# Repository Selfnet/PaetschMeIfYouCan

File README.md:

# P-tschMeIfYouCan
Ein Geschicklichkeitsspiel mit Spaß am Gerät

## Important: Name Entry Keyboard Behavior

This is a required interaction contract. Preserve it when changing the dashboard:

- **Enter in the first displayed input:** move to the second input if its name is empty or whitespace-only; otherwise submit both names and proceed to the leaderboard.
- **Enter in the second displayed input:** submit both names and proceed to the leaderboard, even when either name is blank. Empty or whitespace-only names skip that player's leaderboard entry.
- **Tab / Shift+Tab:** cycle between the name inputs, including wrapping; never submit names or advance to the leaderboard, even when both names are filled.

The inputs are displayed in result order (winner first), not fixed player-number order. These rules apply regardless of which player wins or whether the race is tied. Automatic name-entry timeout is separate from keyboard submission.

[Keyboard regression tests](Test_Server/tests/test_name_entry_keyboard.py) execute the dashboard's actual JavaScript handler. Run them when changing name entry or keyboard handling; they do not test live serial hardware.

## Leaderboard Policy

Each leaderboard shows one row per case-insensitive name, separately for each game mode and leaderboard identity (numbered or named event). Ranks compare each player's **best time**; equal times share a rank. The name uses the latest spelling, and **Set at** is the best attempt's timestamp (the latest matching attempt for equal best times). The **Attempts** column counts all saved scores for that name in the same mode and board, including historical scores. Blank names are still skipped, and retrying a score save does not add an attempt.

First place, including tied first places, is displayed as **Top of Rack**; other ranks remain numeric.

After a race, that player's row is highlighted even when the new time is worse. A worse time appears as **This race** beneath the best time without changing the rank. A first score or strictly improved best earns a compact orange **New PB!** badge; matching an existing best does not. Idle browsing does not show current-race details or badges.

All attempt history remains in SQLite; grouping does not delete or rewrite scores and requires no database migration. A paginated browse freezes the best times, latest attempts, and counts at its opening snapshot. [Leaderboard regression tests](Test_Server/tests/test_leaderboard.py) cover case-insensitive grouping, best-time ranking, attempt counts, and snapshot pagination; [transport tests](Test_Server/tests/test_app.py) cover current-race highlighting and personal-best detection. Neither covers physical hardware or browser layout.

### Explicit Requirement: Post-Race Score Position

When players finish and the post-race leaderboard opens after name entry,
automatically scroll to the faster player from this race and place that
player's score row at the top of the visible list. Choose by this race's time,
not historical personal-best rank. Players must immediately see their placing
without manually searching or scrolling, including beyond the first page.
Preserve the actual leaderboard order and ranks; this requirement changes the
initial scroll position, not the standings.

This is an explicit user requirement. The jump happens once per result view;
manual navigation takes precedence. Ties choose Player 1. If the faster player
skips their name, use the other saved participant; if both skip, stay at the top.
Case-insensitive matching uses the participant's grouped personal-best row.
[Positioning tests](Test_Server/tests/test_result_position.py) cover winner
selection, pagination, ties, skipped names and manual-scroll preservation;
they do not replace native-browser geometry checks.

### Explicit Decision: Current Race Time

The post-race leaderboard must still show the current race time. The main time
and rank remain the player's personal best. If this race was slower, show its
time separately as **This race** beneath the best; if it matched or improved
the best, the main time already shows this race's time. Do not replace or hide
the current result just because an older personal best is faster. Idle browsing
does not show this post-race detail.

### Failed Score Saves

If saving fails while results are open, **Retry saving** resends the captured race,
names, times, mode and captured leaderboard. Automatic return pauses until saving succeeds, then
the leaderboard refreshes and its normal 60-second countdown restarts. Repeated
retries do not add attempts, including when a previous write committed before
reporting an error. Name-entry timeouts and skipped blank names are unchanged.

Back to game, L, Escape and Space require confirmation before abandoning failed
results. Leaving, reset and expiry are blocked during every pending write, including
the initial save. Confirmation gives
up recovery; it does not remove any scores already written. Browser refresh or
reconnection restores recovery from server state, but **restarting the backend
loses unsaved results held in memory**. This is not a durable retry queue.

Browsing another board never dismisses these results. The captured score destination,
save error and Retry saving control remain visible there. A completed save refreshes
the current page snapshot without redirecting an explicitly browsed board.

[Recovery tests](Test_Server/tests/test_score_recovery.py) cover identity,
concurrent requests, idempotence and timeout boundaries;
[recovery UI tests](Test_Server/tests/test_score_recovery_ui.py) execute the actual
dashboard handlers for confirmation, refresh and page invalidation. Neither
replaces browser layout checks or tests live hardware.

## Leaderboard Slots

Use **1-9**, including the numeric keypad, or the slot selector while the game is ready. Outside an active event this selects the next race's scoring slot and switches an open view. During an event, or while stopped or viewing post-race results, it only browses the numbered board. Event-locked digits from the game view open that board for visible feedback. Racing, name entry, maintenance and open dialogs guard the underlying shortcuts. Digits typed into inputs remain input.

Each slot has independent scores and ranks for every game mode. Switching never deletes scores. The manual selection and its selection time are saved in SQLite, independently of browser storage. An event that ends after that selection makes the effective default slot 1, including when the backend was offline for the whole event. Selecting a slot again, even the previously stored slot, records a fresh choice. The destination is captured at race start, so delayed writes cannot move a race to another board.

The database remains at `LEADERBOARD_DB` or `~/.local/share/patchmeifyoucan/leaderboard.sqlite3`. The event migration creates permanent numbered board records and replaces score slot references with stable `leaderboard_id` references. Existing scores keep their IDs, names, durations, timestamps, modes, race/player identities and numbered associations. The manual slot and maintenance setting are retained; migration creates no events. Take fresh verified database and source backups before deployment. Source-only rollback to slot-only code is unsupported, and a database rollback discards scores recorded since its backup.

[Slot persistence and transport tests](Test_Server/tests/test_leaderboard_slots.py) cover migration, isolation, restart restoration, failed settings writes, race identity, and stale page rejection; they do not exercise physical hardware. [Slot keyboard tests](Test_Server/tests/test_leaderboard_slot_keyboard.py) execute the actual dashboard shortcut and selection helpers, including modifier, focus, and phase guards; they do not replace browser layout checks.

## Event Leaderboards

Named events are independent boards, not names attached to slots. Each creation
starts empty, including when its name matches another event. One schedule applies
to all modes, with separate rankings, personal bests, attempt counts and pace
references for each board and mode. Names are trimmed printable text of 1-60
Unicode code points and are displayed as text.

The server assigns both players to the event active at race start, on the half-open
window `start <= now < end`. An active event locks scoring even when a display is
browsing another board. Name entry, delayed saves and retries keep that captured
identity after expiry or End now. Expiry changes future defaults to slot 1 (or an
adjacent active event), never an existing race or explicitly opened view. Race
duration still uses the monotonic clock; event eligibility uses the server's UTC
wall clock. Keep the server clock correct.

The main header shows the currently active event beside the game title in grey,
independent of the viewed leaderboard or captured race. It hides the event name
when no event is active or the display is disconnected.

**L** toggles the leaderboard as before. Opening from the game defaults to the
active event, otherwise the effective numbered selection. Automatic post-race
results always open the captured board. **0**, including the keypad, returns to
the active event and does nothing without one. The Current event button is its
pointer equivalent. Named titles read `Leaderboard - <event name>`; numbered titles
read `Leaderboard`, with the slot shown in the selector. The compact status shows
the next race's destination, or the captured destination while a race is unresolved.

**E** or Past events opens the archive picker only from an open leaderboard.
Events appear newest-ended first, including empty boards, with their Berlin time
ranges. Arrows move focus, Enter selects, Tab stays in the dialog, and Escape/E
closes it and restores focus to Past events. Reopening fetches a fresh list; late
responses cannot reopen a closed picker. The picker blocks underlying shortcuts,
but normal inactivity expiry still closes it. Archive browsing is local and never
redirects scoring or another display. Global manual numbered changes update
ordinary numbered views without evicting archives. Board changes start a fresh
pagination snapshot; renames update titles without losing rows or focus. Current-race
highlighting and winner positioning apply only on the captured result board.

At **/control**, Event leaderboards offers creation, editing, End now and cancellation.
All entered dates/times mean **Europe/Berlin**, even on a browser in another zone.
Start now and event statuses use server time, independent of the browser clock.
The form shows the range before submission; the server
rejects invalid names, overlapping windows, ambiguous/nonexistent DST times and
stale revisions. Rejected or timed-out changes retain inputs and show an error.
Reload events explicitly reloads the selected edit after checking a stale or
unconfirmed change. No change is accepted before storage commits it.

Upcoming events can change their full window or be cancelled after confirmation.
Active events can change their future end or use confirmed End now; their start is
fixed. End now at exactly the start is rejected without changes to preserve a
positive window; retry once server time has advanced. Past events can only be
renamed. There is no past-event or score deletion,
recurrence, historical score move, or added authentication. The control page remains
on the existing trusted-network boundary.

Unknown routing metadata blocks new races visibly instead of choosing a fallback
board. **Retry storage** reloads/reinitializes it without resetting an in-memory
race, recovery or maintenance. After a successful load, the last committed schedule
continues to route while storage is failing. Failed metadata writes cannot change
that schedule. Out-of-band database edits are not supported.

[Policy tests](Test_Server/tests/test_event_policy.py), [storage tests](Test_Server/tests/test_event_storage.py)
and [runtime tests](Test_Server/tests/test_event_runtime.py) cover schedule boundaries,
Berlin/DST validation, migration, immutable capture, revision checks and recovery.
[Player UI tests](Test_Server/tests/test_event_ui.py) and [operator UI tests](Test_Server/tests/test_event_controls.py)
execute the actual JavaScript with controlled DOM/Socket.IO boundaries; they do not
replace native-browser focus/layout checks or physical hardware tests.

## Live Race Statistics

During racing, patches/min uses the median personal-best time from the selected
mode and captured leaderboard as a starting weight of three patches. Each name
counts once, matching the leaderboard; zero-time bests are excluded. The median
is captured once per race and retained on reconnect. Empty or unavailable
leaderboards fall back to the player's own pace. Browsing another board never
changes a running race's reference.

After progress changes, the estimate holds for one estimated patching interval,
then declines if no further progress arrives. The historical weight becomes less
significant as patches accumulate. The rate stays zero before a timed patch; stopped
and completed players show their actual race average. The combined rate uses the
longer player's elapsed time, as before. These display estimates never affect
race times, winners or saved scores.

Each player's lead indicator sits between progress and the clock. Comparable
progress shows the patch gap, with the leading player's indicator highlighted;
ties are neutral and different mode stages are not compared.
[Rate and lead tests](Test_Server/tests/test_dashboard_rates.py) exercise the real
dashboard calculation and rendering; they do not verify kiosk layout or hardware.

## Maintenance Mode

Use the **Maintenance mode** checkbox at `/control` to enable or disable it.
The control page reports **Off**, **Queued** or **Active**. Enabling while ready
activates immediately, including idle leaderboard browsing. During a race,
stopped game, name entry or post-race results, it waits for the normal return to
ready. It never stops a race or dismisses results itself. Uncheck it to cancel
a queued request. A stopped game still needs its normal reset.

While active, every connected dashboard is darkened behind large lowercase
**maintenance mode** text in Selfnet orange and Comic Neue. Dashboard controls
and shortcuts cannot start a game or dismiss the overlay. Disable maintenance
from `/control` to return to ready. Serial observations continue for diagnostics.
Maintenance is an operator convenience on the existing trusted game network,
not authentication or an authorization boundary.

The request is saved in SQLite before it is accepted and is restored across
browser refreshes and backend restarts. A queued request becomes active on
backend restart because races are memory-only. **Do not restart to force queued
maintenance:** it would lose the current race or unsaved results. Failed score
saves still require retry or explicit abandonment; queued maintenance waits for
in-flight saves as well. Failed maintenance-setting writes leave the live setting
unchanged and show an error on `/control`.

Explicit operator policy: if the setting cannot be read at backend startup,
log the error and leave maintenance off. This does not override the separate event
routing safety rule: unknown routing metadata blocks new races until Retry storage
succeeds. A readable saved setting is required for restart
persistence. Migration only adds a default-off settings column; it does not
change scores or the selected slot. Pre-maintenance source ignores this setting,
so a source rollback will no longer block games. Take a fresh database backup
before deployment; maintenance does not itself authorize deployment or restart.

Comic Neue is the approved open-source substitute for Comic Sans. Its bold font
is bundled and served locally, with no OS font installation or external request.
[Dashboard assets](Test_Server/static/dashboard/README.md) records its source and
OFL license; verify the loaded font when checking the maintenance screen.

[Maintenance tests](Test_Server/tests/test_maintenance.py) cover queued
transitions, persistence, recovery and concurrent writes; [UI tests](Test_Server/tests/test_maintenance_ui.py)
exercise the actual overlay, operator and keyboard handlers. Neither verifies
physical hardware, installed fonts or native-browser layout.

## Development

The shared footer keeps instructions visible in every game view. Its leftmost
control, **Space**, can be clicked or activated with the Space key to start, stop
or reset the clock. It is hidden during name entry and leaderboard browsing.
[Dashboard tests](Test_Server/tests/test_dashboard.py) cover phase-dependent
controls; they do not replace native-browser keyboard or layout checks.

[Local preview](docs/local-preview.md) runs the real game with simulated boards
and an isolated, disposable leaderboard. Use it to try the dashboard without
hardware; it does not change or deploy to the game PC.

[Dashboard assets](Test_Server/static/dashboard/README.md) records the original
Selfnet/SIAM sources and font license, not game behavior or deployment.

[Adding gamemodes](docs/gamemode-authoring.md) explains the board/session contract, registry, validation, and scoring identities. Start there when adding a mode; firmware protocols and deployment are outside its scope.

Run `uv run pytest -q` from `Test_Server/`. Node.js must be on `PATH` for the name-entry keyboard tests, which execute the dashboard's JavaScript handler.

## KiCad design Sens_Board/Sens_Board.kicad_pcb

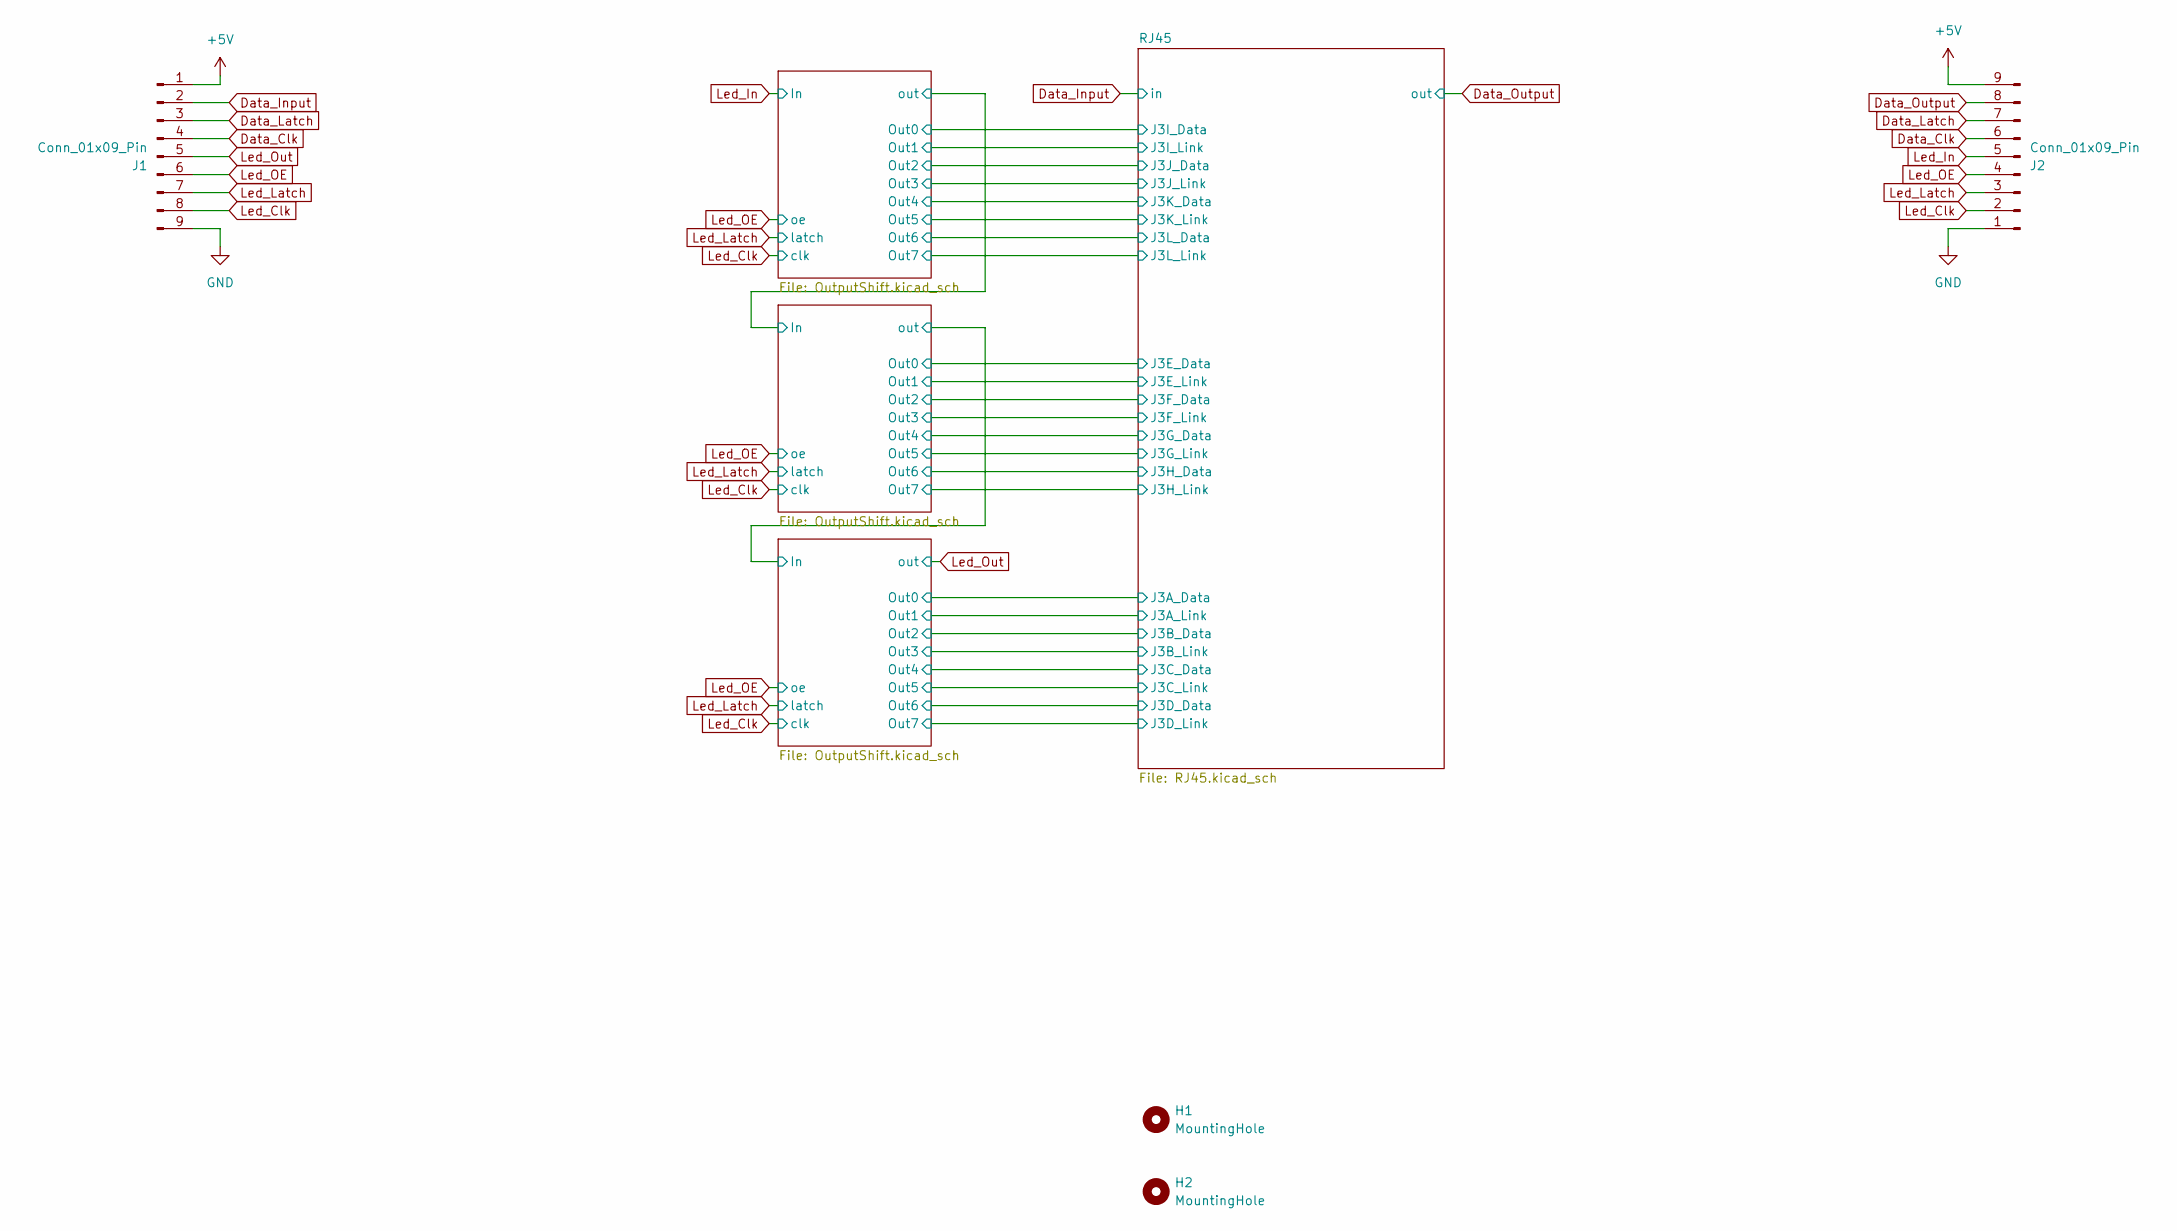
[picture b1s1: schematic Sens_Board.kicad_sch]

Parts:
H1, H2: MountingHole; MountingHole_3.2mm_M3
J1, J2: Conn_01x09_Pin; JST_PH_B9B-PH-SM4-TB_1x09-1MP_P2.00mm_Vertical

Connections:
+5V: J1.1, J2.9; also elsewhere on the board
Data_Clk: J1.4, J2.6; also elsewhere on the board
Data_Input: J1.2; also elsewhere on the board
Data_Latch: J1.3, J2.7; also elsewhere on the board
Data_Output: J2.8; also elsewhere on the board
GND: J1.9, J2.1; also elsewhere on the board
Led_Clk: J1.8, J2.2; also elsewhere on the board
Led_In: J2.5; also elsewhere on the board
Led_Latch: J1.7, J2.3; also elsewhere on the board
Led_OE: J1.6, J2.4; also elsewhere on the board
Led_Out: J1.5; also elsewhere on the board

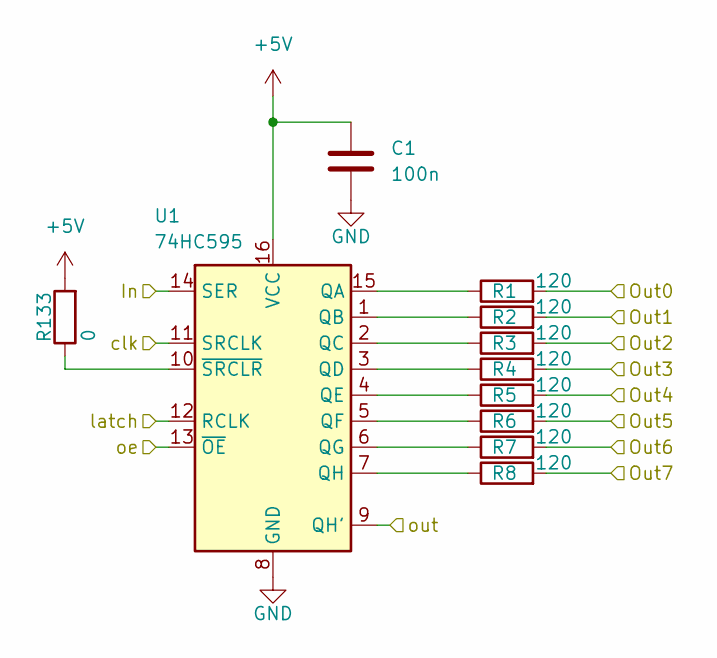
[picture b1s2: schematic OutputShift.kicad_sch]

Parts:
C1: 100n; C_0402_1005Metric
R1, R2, R3, R4, R5, R6, R7, R8: 120; R_0402_1005Metric
R133: 0; R_0402_1005Metric
U1: 74HC595; SOIC-16_4.55x10.3mm_P1.27mm

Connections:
+5V: C1.1, R133.2, U1.16 (VCC); also elsewhere on the board
/OutputShift1/Out0: R1.2; also elsewhere on the board
/OutputShift1/Out1: R2.2; also elsewhere on the board
/OutputShift1/Out2: R3.2; also elsewhere on the board
/OutputShift1/Out3: R4.2; also elsewhere on the board
/OutputShift1/Out4: R5.2; also elsewhere on the board
/OutputShift1/Out5: R6.2; also elsewhere on the board
/OutputShift1/Out6: R7.2; also elsewhere on the board
/OutputShift1/Out7: R8.2; also elsewhere on the board
/OutputShift1/out: U1.9 (QH'); also elsewhere on the board
/OutputShift/out: U1.14 (SER); also elsewhere on the board
GND: C1.2, U1.8 (GND); also elsewhere on the board
Led_Clk: U1.11 (SRCLK); also elsewhere on the board
Led_Latch: U1.12 (RCLK); also elsewhere on the board
Led_OE: U1.13 (~OE); also elsewhere on the board
unnamed: R1.1, U1.15 (QA)
unnamed: R2.1, U1.1 (QB)
unnamed: R3.1, U1.2 (QC)
unnamed: R4.1, U1.3 (QD)
unnamed: R5.1, U1.4 (QE)
unnamed: R6.1, U1.5 (QF)
unnamed: R7.1, U1.6 (QG)
unnamed: R8.1, U1.7 (QH)
unnamed: R133.1, U1.10 (~SRCLR)

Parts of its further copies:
C2, C3: 100n; C_0402_1005Metric
R9, R10, R11, R12, R13, R14, R15, R16, R17, R18, R19, R20, R21, R22, R23, R24: 120; R_0402_1005Metric
R134, R135: 0; R_0402_1005Metric
U2, U3: 74HC595; SOIC-16_4.55x10.3mm_P1.27mm

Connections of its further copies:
+5V: C2.1, C3.1, R134.2, R135.2, U2.16 (VCC), U3.16 (VCC); also elsewhere on the board
/OutputShift1/out: U3.14 (SER); also elsewhere on the board
/OutputShift2/Out0: R17.2; also elsewhere on the board
/OutputShift2/Out1: R18.2; also elsewhere on the board
/OutputShift2/Out2: R19.2; also elsewhere on the board
/OutputShift2/Out3: R20.2; also elsewhere on the board
/OutputShift2/Out4: R21.2; also elsewhere on the board
/OutputShift2/Out5: R22.2; also elsewhere on the board
/OutputShift2/Out6: R23.2; also elsewhere on the board
/OutputShift2/Out7: R24.2; also elsewhere on the board
/OutputShift/Out0: R9.2; also elsewhere on the board
/OutputShift/Out1: R10.2; also elsewhere on the board
/OutputShift/Out2: R11.2; also elsewhere on the board
/OutputShift/Out3: R12.2; also elsewhere on the board
/OutputShift/Out4: R13.2; also elsewhere on the board
/OutputShift/Out5: R14.2; also elsewhere on the board
/OutputShift/Out6: R15.2; also elsewhere on the board
/OutputShift/Out7: R16.2; also elsewhere on the board
/OutputShift/out: U2.9 (QH'); also elsewhere on the board
GND: C2.2, C3.2, U2.8 (GND), U3.8 (GND); also elsewhere on the board
Led_Clk: U2.11 (SRCLK), U3.11 (SRCLK); also elsewhere on the board
Led_In: U2.14 (SER); also elsewhere on the board
Led_Latch: U2.12 (RCLK), U3.12 (RCLK); also elsewhere on the board
Led_OE: U2.13 (~OE), U3.13 (~OE); also elsewhere on the board
Led_Out: U3.9 (QH'); also elsewhere on the board
unnamed: R9.1, U2.15 (QA)
unnamed: R10.1, U2.1 (QB)
unnamed: R11.1, U2.2 (QC)
unnamed: R12.1, U2.3 (QD)
unnamed: R13.1, U2.4 (QE)
unnamed: R14.1, U2.5 (QF)
unnamed: R15.1, U2.6 (QG)
unnamed: R16.1, U2.7 (QH)
unnamed: R134.1, U2.10 (~SRCLR)
unnamed: R17.1, U3.15 (QA)
unnamed: R18.1, U3.1 (QB)
unnamed: R19.1, U3.2 (QC)
unnamed: R20.1, U3.3 (QD)
unnamed: R21.1, U3.4 (QE)
unnamed: R22.1, U3.5 (QF)
unnamed: R23.1, U3.6 (QG)
unnamed: R24.1, U3.7 (QH)
unnamed: R135.1, U3.10 (~SRCLR)

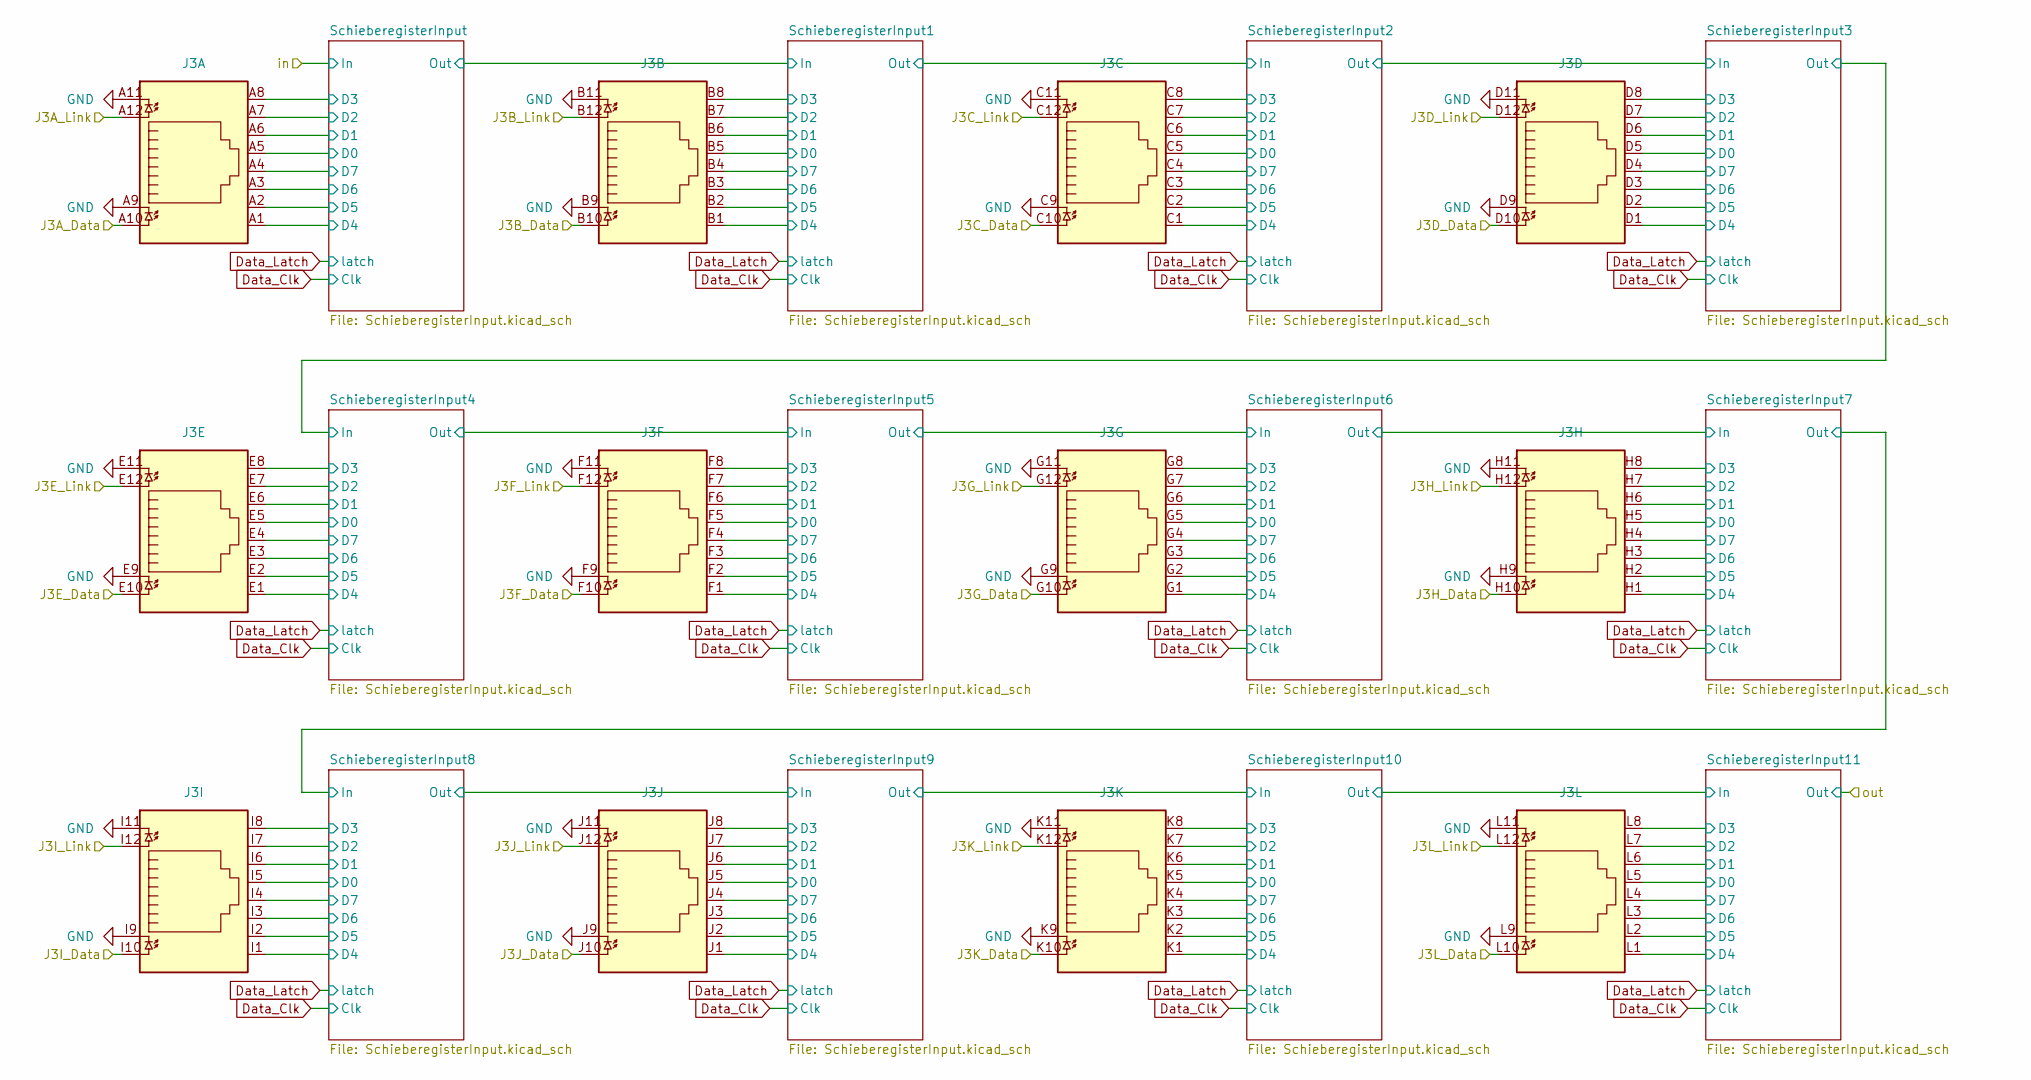
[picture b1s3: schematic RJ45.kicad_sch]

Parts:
J3: RJ45-TH_RJ45-TH_HC-RJ45-059D-2X6-2-04

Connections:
/OutputShift1/Out0: J3.E10; also elsewhere on the board
/OutputShift1/Out1: J3.E12; also elsewhere on the board
/OutputShift1/Out2: J3.F10; also elsewhere on the board
/OutputShift1/Out3: J3.F12; also elsewhere on the board
/OutputShift1/Out4: J3.G10; also elsewhere on the board
/OutputShift1/Out5: J3.G12; also elsewhere on the board
/OutputShift1/Out6: J3.H10; also elsewhere on the board
/OutputShift1/Out7: J3.H12; also elsewhere on the board
/OutputShift2/Out0: J3.A10; also elsewhere on the board
/OutputShift2/Out1: J3.A12; also elsewhere on the board
/OutputShift2/Out2: J3.B10; also elsewhere on the board
/OutputShift2/Out3: J3.B12; also elsewhere on the board
/OutputShift2/Out4: J3.C10; also elsewhere on the board
/OutputShift2/Out5: J3.C12; also elsewhere on the board
/OutputShift2/Out6: J3.D10; also elsewhere on the board
/OutputShift2/Out7: J3.D12; also elsewhere on the board
/OutputShift/Out0: J3.I10; also elsewhere on the board
/OutputShift/Out1: J3.I12; also elsewhere on the board
/OutputShift/Out2: J3.J10; also elsewhere on the board
/OutputShift/Out3: J3.J12; also elsewhere on the board
/OutputShift/Out4: J3.K10; also elsewhere on the board
/OutputShift/Out5: J3.K12; also elsewhere on the board
/OutputShift/Out6: J3.L10; also elsewhere on the board
/OutputShift/Out7: J3.L12; also elsewhere on the board
/RJ45/SchieberegisterInput1/D0: J3.B5; also elsewhere on the board
/RJ45/SchieberegisterInput1/D1: J3.B6; also elsewhere on the board
/RJ45/SchieberegisterInput1/D2: J3.B7; also elsewhere on the board
/RJ45/SchieberegisterInput1/D3: J3.B8; also elsewhere on the board
/RJ45/SchieberegisterInput1/D4: J3.B1; also elsewhere on the board
/RJ45/SchieberegisterInput1/D5: J3.B2; also elsewhere on the board
/RJ45/SchieberegisterInput1/D6: J3.B3; also elsewhere on the board
/RJ45/SchieberegisterInput1/D7: J3.B4; also elsewhere on the board
/RJ45/SchieberegisterInput2/D0: J3.C5; also elsewhere on the board
/RJ45/SchieberegisterInput2/D1: J3.C6; also elsewhere on the board
/RJ45/SchieberegisterInput2/D2: J3.C7; also elsewhere on the board
/RJ45/SchieberegisterInput2/D3: J3.C8; also elsewhere on the board
/RJ45/SchieberegisterInput2/D4: J3.C1; also elsewhere on the board
/RJ45/SchieberegisterInput2/D5: J3.C2; also elsewhere on the board
/RJ45/SchieberegisterInput2/D6: J3.C3; also elsewhere on the board
/RJ45/SchieberegisterInput2/D7: J3.C4; also elsewhere on the board
/RJ45/SchieberegisterInput3/D0: J3.D5; also elsewhere on the board
/RJ45/SchieberegisterInput3/D1: J3.D6; also elsewhere on the board
/RJ45/SchieberegisterInput3/D2: J3.D7; also elsewhere on the board
/RJ45/SchieberegisterInput3/D3: J3.D8; also elsewhere on the board
/RJ45/SchieberegisterInput3/D4: J3.D1; also elsewhere on the board
/RJ45/SchieberegisterInput3/D5: J3.D2; also elsewhere on the board
/RJ45/SchieberegisterInput3/D6: J3.D3; also elsewhere on the board
/RJ45/SchieberegisterInput3/D7: J3.D4; also elsewhere on the board
/RJ45/SchieberegisterInput4/D0: J3.E5; also elsewhere on the board
/RJ45/SchieberegisterInput4/D1: J3.E6; also elsewhere on the board
/RJ45/SchieberegisterInput4/D2: J3.E7; also elsewhere on the board
/RJ45/SchieberegisterInput4/D3: J3.E8; also elsewhere on the board
/RJ45/SchieberegisterInput4/D4: J3.E1; also elsewhere on the board
/RJ45/SchieberegisterInput4/D5: J3.E2; also elsewhere on the board
/RJ45/SchieberegisterInput4/D6: J3.E3; also elsewhere on the board
/RJ45/SchieberegisterInput4/D7: J3.E4; also elsewhere on the board
/RJ45/SchieberegisterInput5/D0: J3.F5; also elsewhere on the board
/RJ45/SchieberegisterInput5/D1: J3.F6; also elsewhere on the board
/RJ45/SchieberegisterInput5/D2: J3.F7; also elsewhere on the board
/RJ45/SchieberegisterInput5/D3: J3.F8; also elsewhere on the board
/RJ45/SchieberegisterInput5/D4: J3.F1; also elsewhere on the board
/RJ45/SchieberegisterInput5/D5: J3.F2; also elsewhere on the board
/RJ45/SchieberegisterInput5/D6: J3.F3; also elsewhere on the board
/RJ45/SchieberegisterInput5/D7: J3.F4; also elsewhere on the board
/RJ45/SchieberegisterInput6/D0: J3.G5; also elsewhere on the board
/RJ45/SchieberegisterInput6/D1: J3.G6; also elsewhere on the board
/RJ45/SchieberegisterInput6/D2: J3.G7; also elsewhere on the board
/RJ45/SchieberegisterInput6/D3: J3.G8; also elsewhere on the board
/RJ45/SchieberegisterInput6/D4: J3.G1; also elsewhere on the board
/RJ45/SchieberegisterInput6/D5: J3.G2; also elsewhere on the board
/RJ45/SchieberegisterInput6/D6: J3.G3; also elsewhere on the board
/RJ45/SchieberegisterInput6/D7: J3.G4; also elsewhere on the board
/RJ45/SchieberegisterInput7/D0: J3.H5; also elsewhere on the board
/RJ45/SchieberegisterInput7/D1: J3.H6; also elsewhere on the board
/RJ45/SchieberegisterInput7/D2: J3.H7; also elsewhere on the board
/RJ45/SchieberegisterInput7/D3: J3.H8; also elsewhere on the board
/RJ45/SchieberegisterInput7/D4: J3.H1; also elsewhere on the board
/RJ45/SchieberegisterInput7/D5: J3.H2; also elsewhere on the board
/RJ45/SchieberegisterInput7/D6: J3.H3; also elsewhere on the board
/RJ45/SchieberegisterInput7/D7: J3.H4; also elsewhere on the board
/RJ45/SchieberegisterInput8/D0: J3.I5; also elsewhere on the board
/RJ45/SchieberegisterInput8/D1: J3.I6; also elsewhere on the board
/RJ45/SchieberegisterInput8/D2: J3.I7; also elsewhere on the board
/RJ45/SchieberegisterInput8/D3: J3.I8; also elsewhere on the board
/RJ45/SchieberegisterInput8/D4: J3.I1; also elsewhere on the board
/RJ45/SchieberegisterInput8/D5: J3.I2; also elsewhere on the board
/RJ45/SchieberegisterInput8/D6: J3.I3; also elsewhere on the board
/RJ45/SchieberegisterInput8/D7: J3.I4; also elsewhere on the board
/RJ45/SchieberegisterInput9/D0: J3.J5; also elsewhere on the board
/RJ45/SchieberegisterInput9/D1: J3.J6; also elsewhere on the board
/RJ45/SchieberegisterInput9/D2: J3.J7; also elsewhere on the board
/RJ45/SchieberegisterInput9/D3: J3.J8; also elsewhere on the board
/RJ45/SchieberegisterInput9/D4: J3.J1; also elsewhere on the board
/RJ45/SchieberegisterInput9/D5: J3.J2; also elsewhere on the board
/RJ45/SchieberegisterInput9/D6: J3.J3; also elsewhere on the board
/RJ45/SchieberegisterInput9/D7: J3.J4; also elsewhere on the board
/RJ45/SchieberegisterInput10/D0: J3.K5; also elsewhere on the board
/RJ45/SchieberegisterInput10/D1: J3.K6; also elsewhere on the board
/RJ45/SchieberegisterInput10/D2: J3.K7; also elsewhere on the board
/RJ45/SchieberegisterInput10/D3: J3.K8; also elsewhere on the board
/RJ45/SchieberegisterInput10/D4: J3.K1; also elsewhere on the board
/RJ45/SchieberegisterInput10/D5: J3.K2; also elsewhere on the board
/RJ45/SchieberegisterInput10/D6: J3.K3; also elsewhere on the board
/RJ45/SchieberegisterInput10/D7: J3.K4; also elsewhere on the board
/RJ45/SchieberegisterInput11/D0: J3.L5; also elsewhere on the board
/RJ45/SchieberegisterInput11/D1: J3.L6; also elsewhere on the board
/RJ45/SchieberegisterInput11/D2: J3.L7; also elsewhere on the board
/RJ45/SchieberegisterInput11/D3: J3.L8; also elsewhere on the board
/RJ45/SchieberegisterInput11/D4: J3.L1; also elsewhere on the board
/RJ45/SchieberegisterInput11/D5: J3.L2; also elsewhere on the board
/RJ45/SchieberegisterInput11/D6: J3.L3; also elsewhere on the board
/RJ45/SchieberegisterInput11/D7: J3.L4; also elsewhere on the board
/RJ45/SchieberegisterInput/D0: J3.A5; also elsewhere on the board
/RJ45/SchieberegisterInput/D1: J3.A6; also elsewhere on the board
/RJ45/SchieberegisterInput/D2: J3.A7; also elsewhere on the board
/RJ45/SchieberegisterInput/D3: J3.A8; also elsewhere on the board
/RJ45/SchieberegisterInput/D4: J3.A1; also elsewhere on the board
/RJ45/SchieberegisterInput/D5: J3.A2; also elsewhere on the board
/RJ45/SchieberegisterInput/D6: J3.A3; also elsewhere on the board
/RJ45/SchieberegisterInput/D7: J3.A4; also elsewhere on the board
GND: J3.A9, J3.A11, J3.B9, J3.B11, J3.C9, J3.C11, J3.D9, J3.D11, J3.E9, J3.E11, J3.F9, J3.F11, J3.G9, J3.G11, J3.H9, J3.H11, J3.I9, J3.I11, J3.J9, J3.J11, J3.K9, J3.K11, J3.L9, J3.L11; also elsewhere on the board

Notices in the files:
README.md:
Selfnet/SIAM sources and font license, not game behavior or deployment.
